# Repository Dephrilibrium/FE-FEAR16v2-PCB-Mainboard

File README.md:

# FEAR-Mainboard
This repository contains the KiCAD-design files of the F(ield) E(mission) A(rray) R(egulation) current control circuit board.

Note: This project is part of the SubModule-repository [FE-FEAR16v2][FE-FEAR16v2-SubmoduleRepo], where you can find sub-repositories for shield-PCBs and the firmware.

# Description
The board has two areas. A low-voltage side (5V USB for computer connection, top left) which is galvanically isolated up to 1500V from the high voltage side (rest of the PCB).

The board uses a USB-C jack on the low-voltage side of the board for communication. The USB-C can also be used as AC power supply, but for this, a USB-Hub with an AC-power adapter is recommended (depending on the amount of shields and their power-use). Alternatively, a 12V screw-terminal is added as option for an external 12V AC power supply. The option if 5V USB or 12V external supply is selected by a solder-jumper. (Note: +5V or +12V needs different DCDC converter types for the +-15V supply voltage on the high-voltage side!)

The board communicates via USB by providing a virtual COM-Port on the computer. The serial connection from the FT232 for board-internal communication is transferred from the low-voltage side to the high-voltage side via optocouplers and there connected to a TIVA-Launchpad, providing the microcontroller (µC). The Launchpad runs a terminal where you can query different commands e.g. querying measurement values, etc. The µC uses SPI connections for the ADCs and DACs.

ADCs and DACs have different supplies for logic (digital signals) and references (analog) and provide 2 ADC-inputs (VShnt0..15 and VDrp0..15) for measurements and 1x DAC-output (DAC0..15) for controls to each of the shields. Each ADC and DAC has only 8 inputs. Therefore, 2 of them each can be daisy-chained together to achieve 16 in-/outputs for VShnt, VDrp and DAC.

The ADC and DAC range is by default &pm;10V. However, the ranges can be adjusted within the firmware in the ADC/DAC-wrapper sourcecodes.

# Firmware
The board-firmware can be found in the [FE-FEAR16v2 Submodule-Repo][FE-FEAR16v2-SubmoduleRepo] and needs to be flashed onto the µC of the LaunchPad. Instructions and command-documentation can be found in the firmware-repository.

# Daisy-Chains
ADCs and DACs only have 8 In-/Outputs per chip. For enough In-/Outputs for up to 16 shields, 2 ADCs or DACs can be daisy-chained together. 1 and 2 chips per ADC- and DAC-chain were tested. When using only 1 chip per ADC-/DAC-chain, the MISO (SPI data in) and MOSI (SPI data out) pins of the empty ADC-footprint needs to be shorted. The connection is indicated by the silk-screen:

The firmware handles this via software defines (described in the firmware-repository).

[FE-FEAR16v2-SubmoduleRepo]: https://github.com/Dephrilibrium/FE-FEAR16v2

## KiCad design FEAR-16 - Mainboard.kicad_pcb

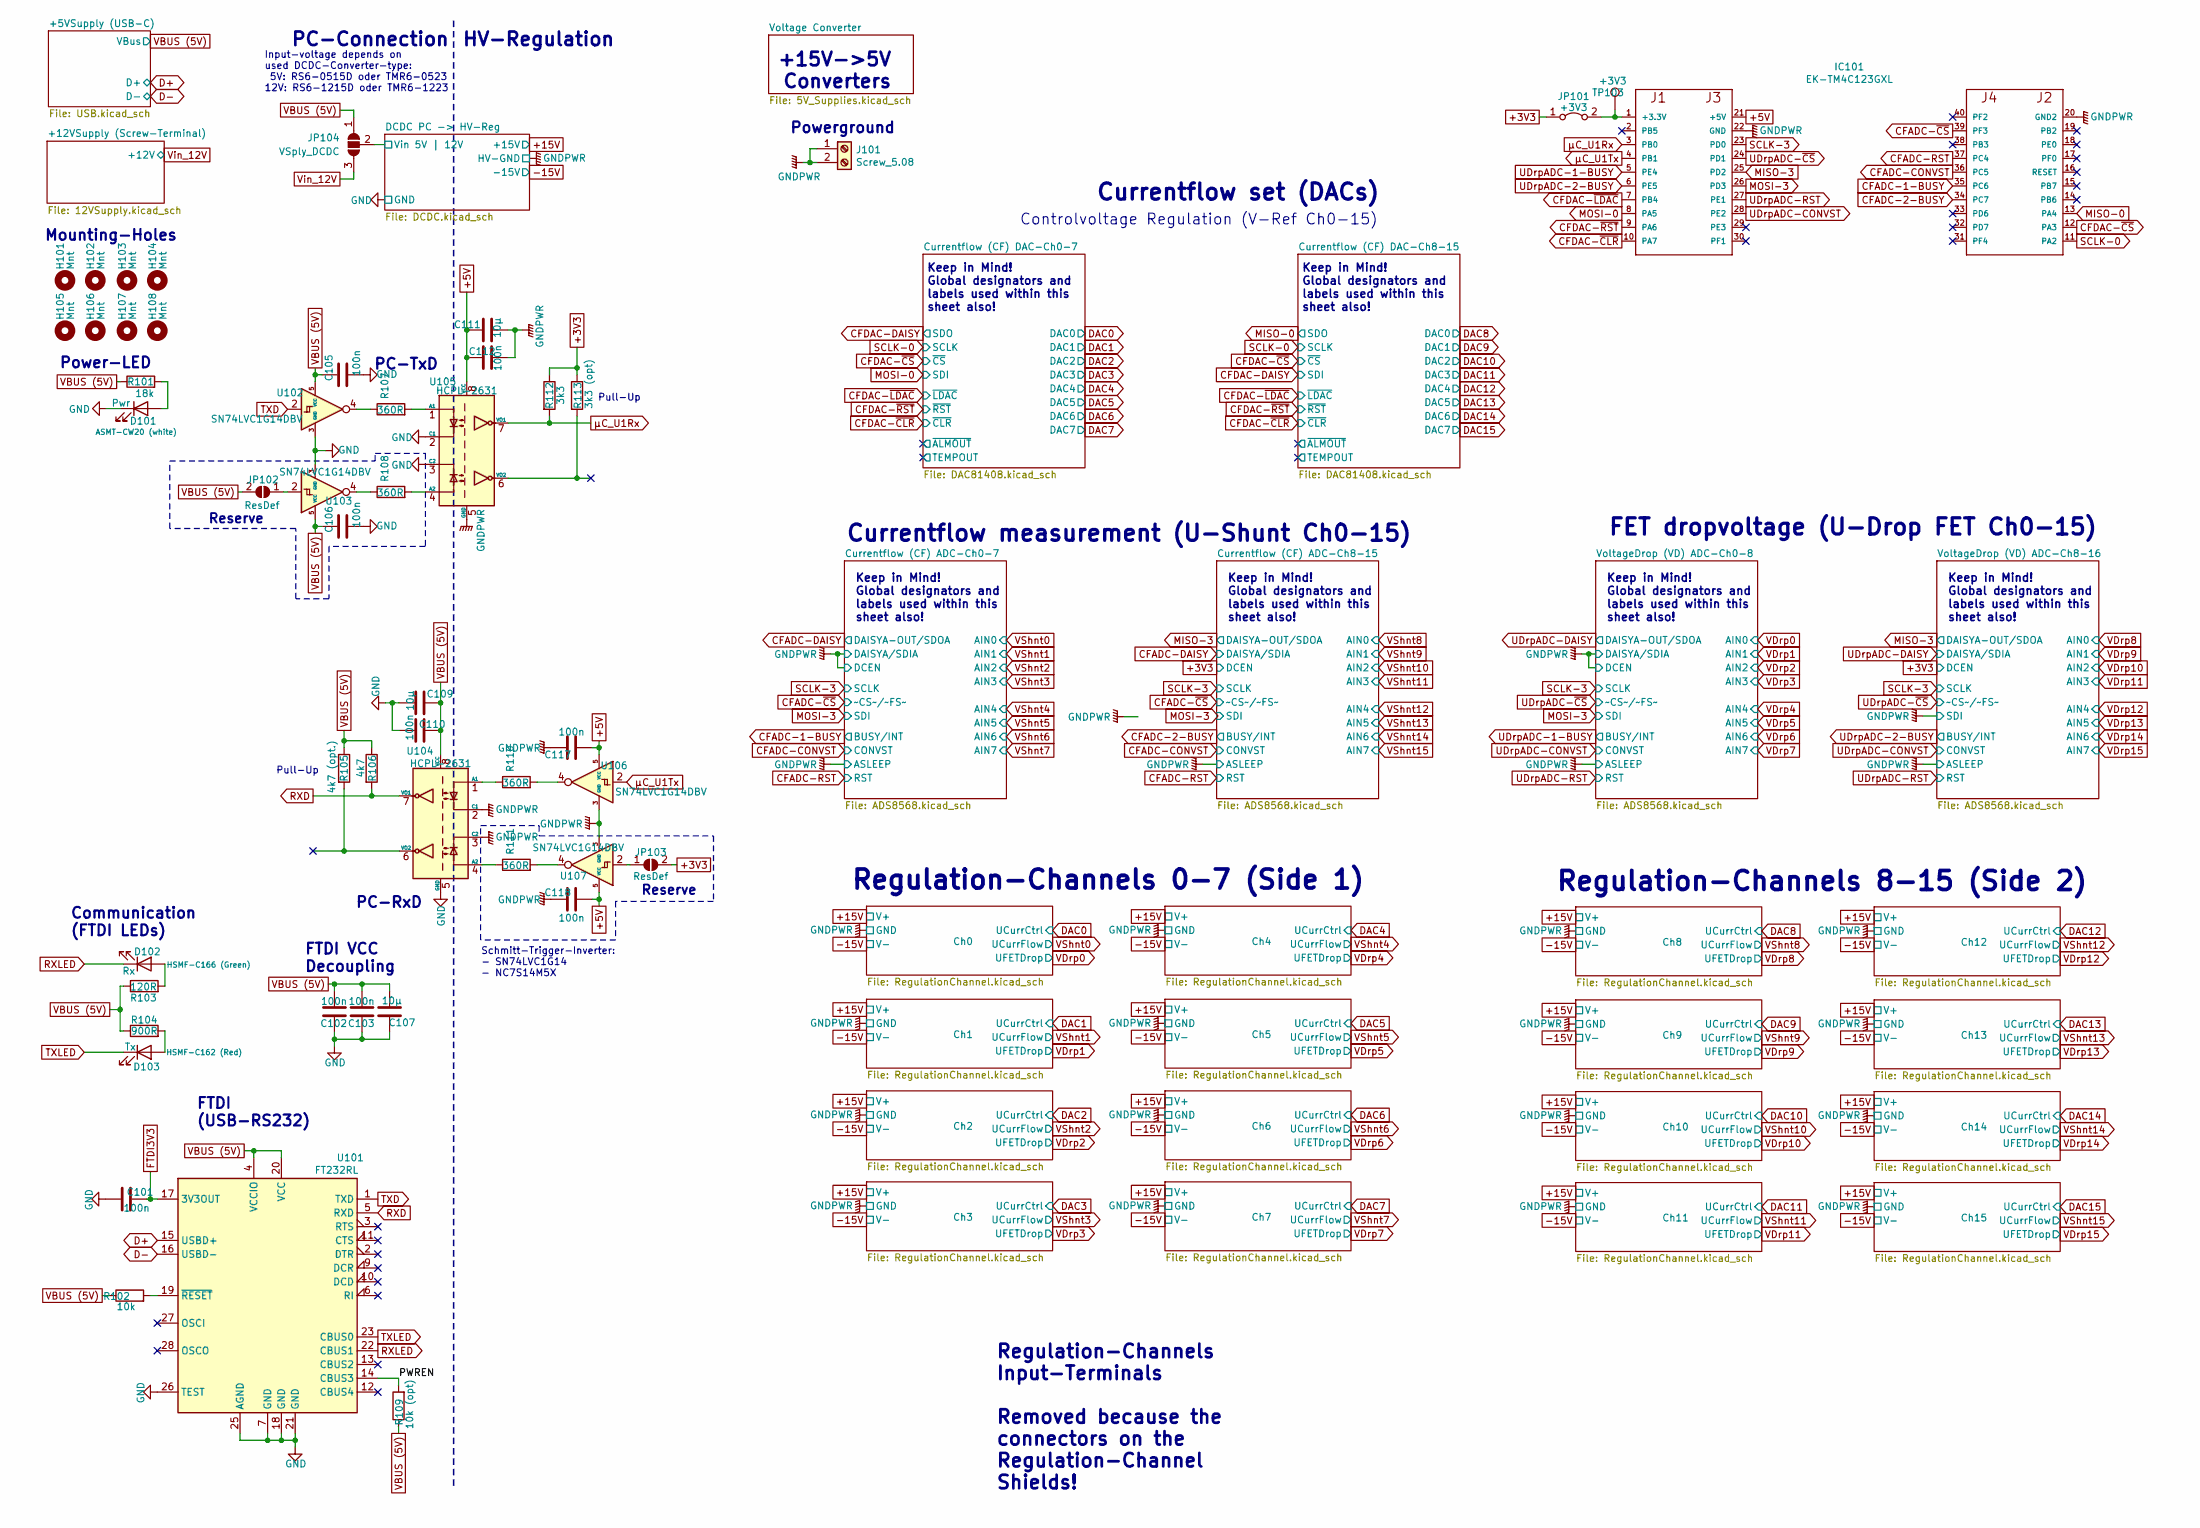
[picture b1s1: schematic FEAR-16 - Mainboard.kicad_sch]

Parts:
C101, C102, C103, C105, C106, C110, C112, C117, C118: 100n; C_0603_1608Metric
C107, C109, C111: 10µ; C_0805_2012Metric
D101: Pwr; LED_0603_1608Metric
D102: Rx; LED_0603_1608Metric
D103: Tx; LED_0603_1608Metric
H101, H102, H103, H104, H105, H106, H107, H108: Mnt; MountingHole_3.2mm_M3
IC101: EK-TM4C123GXL; TM4C123LAUNCHPAD
J101: Screw_5.08; TerminalBlock_RND_205-00232_1x02_P5.08mm_Horizontal
JP101: +3V3; PinHeader_1x02_P2.54mm_Vertical
JP102, JP103: ResDef; SolderJumper-2_P1.3mm_Open_RoundedPad1.0x1.5mm
JP104: VSply_DCDC; SolderJumper-3_P1.3mm_Open_RoundedPad1.0x1.5mm
R101: 18k; R_0603_1608Metric
R102: 10k; R_0603_1608Metric
R103: 120R; R_0603_1608Metric
R104: 900R; R_0603_1608Metric
R105: 4k7 (opt.); R_0603_1608Metric
R106: 4k7; R_0603_1608Metric
R107, R108, R110, R111: 360R; R_0603_1608Metric
R109: 10k (opt); R_0603_1608Metric
R112: 3k3; R_0603_1608Metric
R113: 3k3 (opt); R_0603_1608Metric
TP103: +3V3; TestPoint_Pad_D1.5mm
U101: FT232RL; SSOP-28_5.3x10.2mm_P0.65mm
U102, U103, U106, U107: SN74LVC1G14DBV; SOT-23-5
U104, U105: HCPL-2631; DIP-8_W7.62mm

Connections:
+3V3: JP101.1 (A), JP103.2 (B), R112.1, R113.1; also elsewhere on the board
+5V: C111.1, C112.2, C117.1, C118.1, IC101.21 (+5V), U105.8 (VCC), U106.5 (VCC), U107.5 (VCC); also elsewhere on the board
/DCDC PC -> HV-Reg/Vin 5V | 12V: JP104.2 (C); also elsewhere on the board
/PWREN: R109.2, U101.14 (CBUS3)
CFADC-1-BUSY: IC101.35 (PC6); also elsewhere on the board
CFADC-2-BUSY: IC101.34 (PC7); also elsewhere on the board
CFADC-CONVST: IC101.36 (PC5); also elsewhere on the board
CFADC-RST: IC101.37 (PC4); also elsewhere on the board
CFADC-~CS: IC101.39 (PF3); also elsewhere on the board
CFDAC-~CLR: IC101.10 (PA7); also elsewhere on the board
CFDAC-~CS: IC101.12 (PA3); also elsewhere on the board
CFDAC-~LDAC: IC101.7 (PB4); also elsewhere on the board
CFDAC-~RST: IC101.9 (PA6); also elsewhere on the board
D+: U101.15 (USBD+); also elsewhere on the board
D-: U101.16 (USBD-); also elsewhere on the board
FTDI3V3: C101.2, U101.17 (3V3OUT)
GND: C101.1, C102.1, C103.1, C105.2, C106.2, C107.2, C109.2, C110.1, D101.1 (K), U101.7 (GND), U101.18 (GND), U101.21 (GND), U101.25 (AGND), U101.26 (TEST), U102.3 (GND), U103.3 (GND), U104.5 (GND), U105.2 (C1), U105.3 (C2); also elsewhere on the board
GNDPWR: C111.2, C112.1, C117.2, C118.2, IC101.20 (GND2), IC101.22 (GND), J101.1, J101.2, U104.2 (C1), U104.3 (C2), U105.5 (GND), U106.3 (GND), U107.3 (GND); also elsewhere on the board
MISO-0: IC101.13 (PA4); also elsewhere on the board
MISO-3: IC101.25 (PD2); also elsewhere on the board
MOSI-0: IC101.8 (PA5); also elsewhere on the board
MOSI-3: IC101.26 (PD3); also elsewhere on the board
unnamed: D101.2 (A), R101.2
unnamed: D102.2 (A), R103.2
unnamed: D103.2 (A), R104.2
unnamed: IC101.1 (+3.3V), JP101.2 (B), TP103.1
unnamed: JP102.1 (A), U103.2
unnamed: JP103.1 (A), U107.2
unnamed: R107.1, U102.4
unnamed: R108.1, U103.4
unnamed: R110.2, U106.4
unnamed: R111.2, U107.4
unnamed: R102.2, U101.19 (~RESET)
unnamed: R110.1, U104.1 (A1)
unnamed: R111.1, U104.4 (A2)
unnamed: R107.2, U105.1 (A1)
unnamed: R108.2, U105.4 (A2)
RXD: R106.2, U101.5 (RXD), U104.7 (VO1)
RXLED: D102.1 (K), U101.22 (CBUS1)
SCLK-0: IC101.11 (PA2); also elsewhere on the board
SCLK-3: IC101.23 (PD0); also elsewhere on the board
TXD: U101.1 (TXD), U102.2
TXLED: D103.1 (K), U101.23 (CBUS0)
UDrpADC-1-BUSY: IC101.5 (PE4); also elsewhere on the board
UDrpADC-2-BUSY: IC101.6 (PE5); also elsewhere on the board
UDrpADC-CONVST: IC101.28 (PE2); also elsewhere on the board
UDrpADC-RST: IC101.27 (PE1); also elsewhere on the board
UDrpADC-~CS: IC101.24 (PD1); also elsewhere on the board
VBUS (5V): C102.2, C103.2, C105.1, C106.1, C107.1, C109.1, C110.2, JP102.2 (B), JP104.1 (A), R101.1, R102.1, R103.1, R104.1, R105.1, R106.1, R109.1, U101.4 (VCCIO), U101.20 (VCC), U102.5 (VCC), U103.5 (VCC), U104.8 (VCC); also elsewhere on the board
Vin_12V: JP104.3 (B); also elsewhere on the board
µC_U1Rx: IC101.3 (PB0), R112.2, U105.7 (VO1)
µC_U1Tx: IC101.4 (PB1), U106.2

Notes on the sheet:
Power-LED
Controlvoltage Regulation (V-Ref Ch0-15)
Keep in Mind! Global designators and labels used within this sheet also!
Reserve
Regulation-Channels 8-15 (Side 2)
Regulation-Channels Input-Terminals Removed because the connectors on the Regulation-Channel Shields!
Mounting-Holes
FTDI (USB-RS232)
HV-Regulation
PC-RxD
Input-voltage depends on used DCDC-Converter-type: 5V: RS6-0515D oder TMR6-0523 12V: RS6-1215D oder TMR6-1223
Communication (FTDI LEDs)
Regulation-Channels 0-7 (Side 1)
Pull-Up
Powerground
Currentflow measurement (U-Shunt Ch0-15)
FET dropvoltage (U-Drop FET Ch0-15)
PC-TxD
Currentflow set (DACs)
PC-Connection
+15V->5V Converters
Schmitt-Trigger-Inverter: - SN74LVC1G14 - NC7S14M5X
FTDI VCC Decoupling

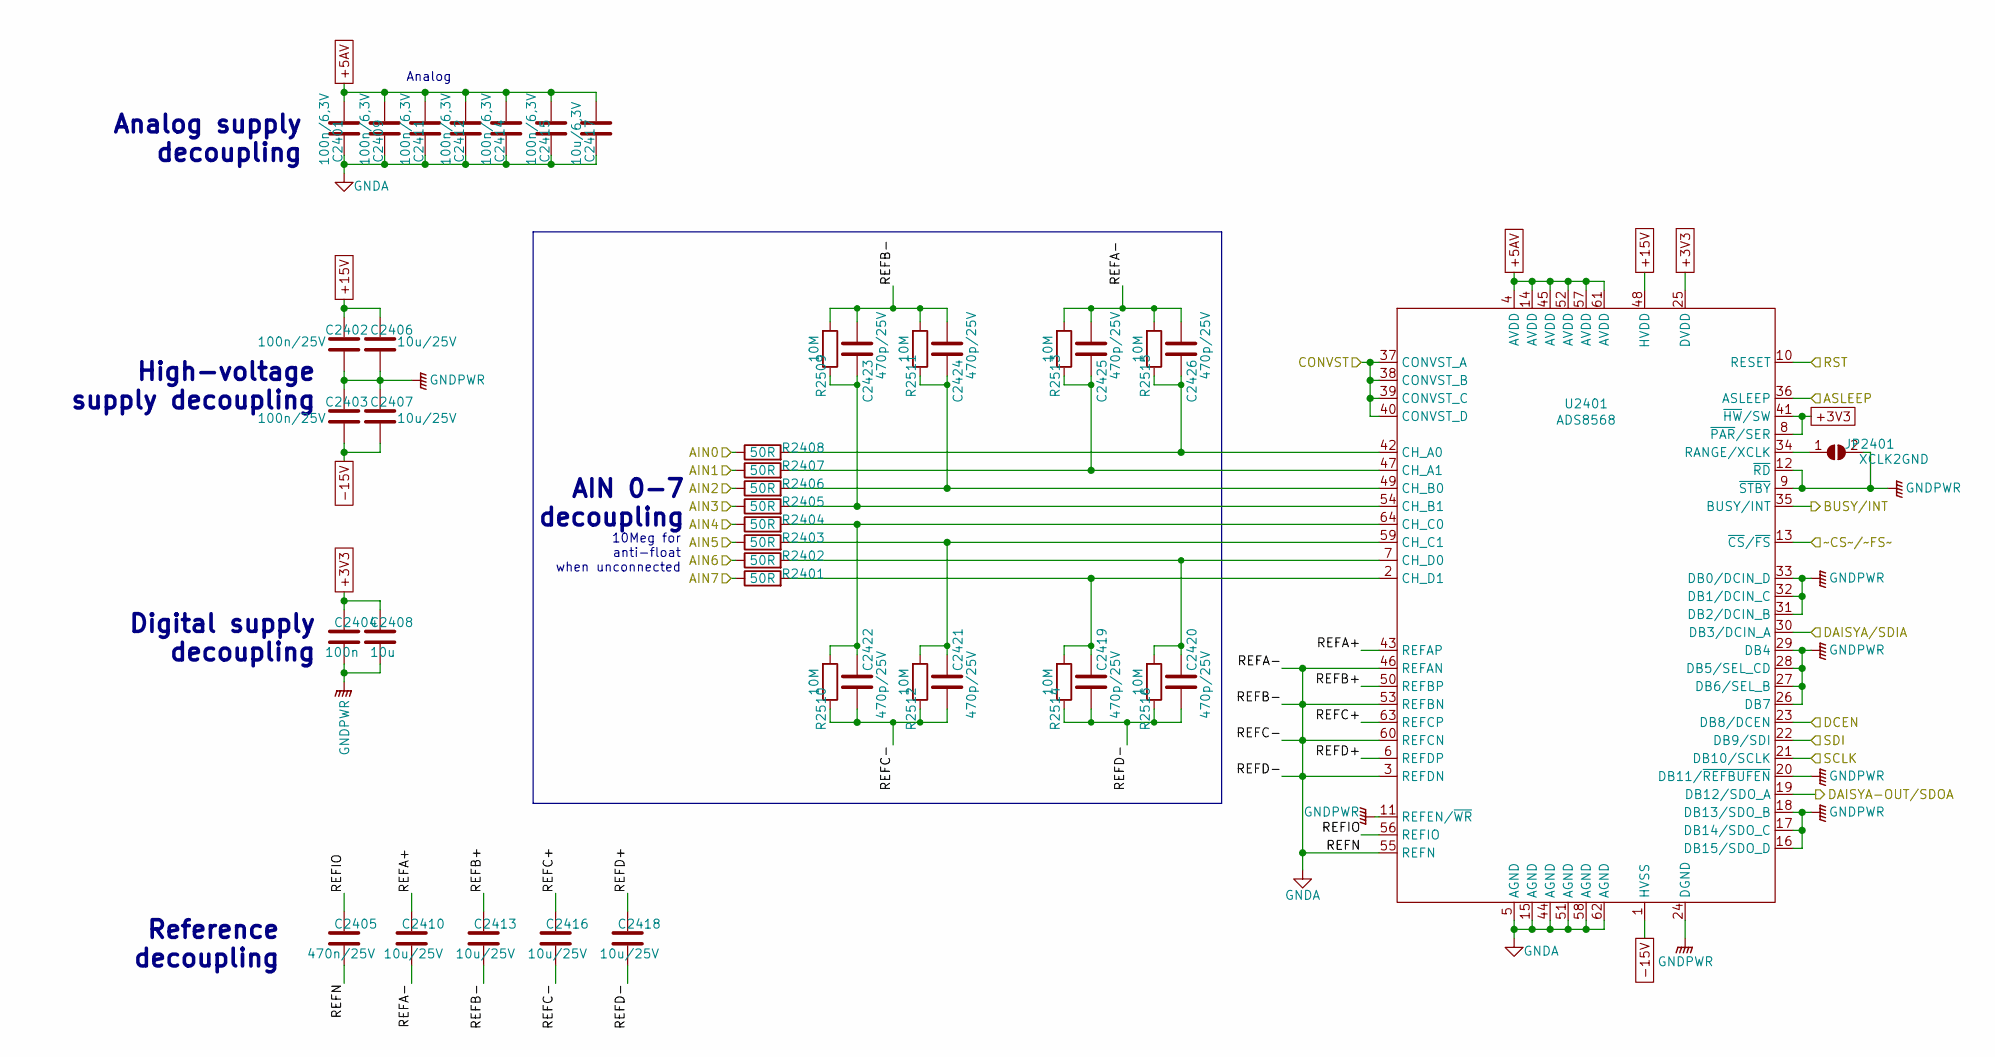
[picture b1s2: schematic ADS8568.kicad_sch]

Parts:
C2401, C2409, C2411, C2412, C2414, C2415: 100n/6,3V; C_0603_1608Metric
C2402, C2403: 100n/25V; C_0603_1608Metric
C2404: 100n; C_0603_1608Metric
C2405: 470n/25V; C_0603_1608Metric
C2406, C2407, C2410, C2413, C2416, C2418: 10u/25V; C_0805_2012Metric
C2408: 10u; C_0805_2012Metric
C2417: 10u/6,3V; C_0805_2012Metric
C2419, C2420, C2421, C2422, C2423, C2424, C2425, C2426: 470p/25V; C_0603_1608Metric
JP2401: XCLK2GND; Jumper_0.5x0.5
R2401, R2402, R2403, R2404, R2405, R2406, R2407, R2408: 50R; R_0603_1608Metric
R2509, R2510, R2511, R2512, R2513, R2514, R2515, R2516: 10M; R_0603_1608Metric
U2401: ADS8568; LQFP-64_10x10mm_P0.5mm

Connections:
+3V3: C2404.1, C2408.1, U2401.8 (~PAR/SER), U2401.25 (DVDD), U2401.41 (~HW/SW); also elsewhere on the board
+5AV: C2401.1, C2409.1, C2411.1, C2412.1, C2414.1, C2415.1, C2417.1, U2401.4 (AVDD), U2401.14 (AVDD), U2401.45 (AVDD), U2401.52 (AVDD), U2401.57 (AVDD), U2401.61 (AVDD); also elsewhere on the board
+15V: C2402.1, C2406.1, U2401.48 (HVDD); also elsewhere on the board
-15V: C2403.2, C2407.2, U2401.1 (HVSS); also elsewhere on the board
/VoltageDrop (VD) ADC-Ch0-8/REFA+: C2410.1, U2401.43 (REFAP)
/VoltageDrop (VD) ADC-Ch0-8/REFB+: C2413.1, U2401.50 (REFBP)
/VoltageDrop (VD) ADC-Ch0-8/REFC+: C2416.1, U2401.63 (REFCP)
/VoltageDrop (VD) ADC-Ch0-8/REFD+: C2418.1, U2401.6 (REFDP)
/VoltageDrop (VD) ADC-Ch0-8/REFIO: C2405.1, U2401.56 (REFIO)
GNDA: C2401.2, C2405.2, C2409.2, C2410.2, C2411.2, C2412.2, C2413.2, C2414.2, C2415.2, C2416.2, C2417.2, C2418.2, C2419.2, C2420.2, C2421.2, C2422.2, C2423.2, C2424.2, C2425.2, C2426.2, R2509.2, R2510.1, R2511.2, R2512.1, R2513.2, R2514.1, R2515.2, R2516.1, U2401.3 (REFDN), U2401.5 (AGND), U2401.15 (AGND), U2401.44 (AGND), U2401.46 (REFAN), U2401.51 (AGND), U2401.53 (REFBN), U2401.55 (REFN), U2401.58 (AGND), U2401.60 (REFCN), U2401.62 (AGND); also elsewhere on the board
GNDPWR: C2402.2, C2403.1, C2404.2, C2406.2, C2407.1, C2408.2, JP2401.2 (B), U2401.9 (~STBY), U2401.11 (REFEN/~WR), U2401.12 (~RD), U2401.16 (DB15/SDO_D), U2401.17 (DB14/SDO_C), U2401.18 (DB13/SDO_B), U2401.20 (DB11/~REFBUFEN), U2401.23 (DB8/DCEN), U2401.24 (DGND), U2401.26 (DB7), U2401.27 (DB6/SEL_B), U2401.28 (DB5/SEL_CD), U2401.29 (DB4), U2401.30 (DB3/DCIN_A), U2401.31 (DB2/DCIN_B), U2401.32 (DB1/DCIN_C), U2401.33 (DB0/DCIN_D), U2401.36 (ASLEEP); also elsewhere on the board
MOSI-3: U2401.22 (DB9/SDI); also elsewhere on the board
unnamed: JP2401.1 (A), U2401.34 (RANGE/XCLK)
unnamed: C2426.1, R2408.2, R2515.1, U2401.42 (CH_A0)
unnamed: C2425.1, R2407.2, R2513.1, U2401.47 (CH_A1)
unnamed: C2424.1, R2406.2, R2511.1, U2401.49 (CH_B0)
unnamed: C2423.1, R2405.2, R2509.1, U2401.54 (CH_B1)
unnamed: C2422.1, R2404.2, R2510.2, U2401.64 (CH_C0)
unnamed: C2421.1, R2403.2, R2512.2, U2401.59 (CH_C1)
unnamed: C2420.1, R2402.2, R2516.2, U2401.7 (CH_D0)
unnamed: C2419.1, R2401.2, R2514.2, U2401.2 (CH_D1)
SCLK-3: U2401.21 (DB10/SCLK); also elsewhere on the board
UDrpADC-1-BUSY: U2401.35 (BUSY/INT); also elsewhere on the board
UDrpADC-CONVST: U2401.37 (CONVST_A), U2401.38 (CONVST_B), U2401.39 (CONVST_C), U2401.40 (CONVST_D); also elsewhere on the board
UDrpADC-DAISY: U2401.19 (DB12/SDO_A); also elsewhere on the board
UDrpADC-RST: U2401.10 (RESET); also elsewhere on the board
UDrpADC-~CS: U2401.13 (~CS/~FS); also elsewhere on the board
VDrp0: R2408.1; also elsewhere on the board
VDrp1: R2407.1; also elsewhere on the board
VDrp2: R2406.1; also elsewhere on the board
VDrp3: R2405.1; also elsewhere on the board
VDrp4: R2404.1; also elsewhere on the board
VDrp5: R2403.1; also elsewhere on the board
VDrp6: R2402.1; also elsewhere on the board
VDrp7: R2401.1; also elsewhere on the board

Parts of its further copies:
C1301, C1309, C1311, C1312, C1314, C1315, C2201, C2209, C2211, C2212, C2214, C2215, C2501, C2509, C2511, C2512, C2514, C2515: 100n/6,3V; C_0603_1608Metric
C1302, C1303, C2202, C2203, C2502, C2503: 100n/25V; C_0603_1608Metric
C1304, C2204, C2504: 100n; C_0603_1608Metric
C1305, C2205, C2505: 470n/25V; C_0603_1608Metric
C1306, C1307, C1310, C1313, C1316, C1318, C2206, C2207, C2210, C2213, C2216, C2218, C2506, C2507, C2510, C2513, C2516, C2518: 10u/25V; C_0805_2012Metric
C1308, C2208, C2508: 10u; C_0805_2012Metric
C1317, C2217, C2517: 10u/6,3V; C_0805_2012Metric
C1319, C1320, C1321, C1322, C1323, C1324, C1325, C1326, C2219, C2220, C2221, C2222, C2223, C2224, C2225, C2226, C2519, C2520, C2521, C2522, C2523, C2524, C2525, C2526: 470p/25V; C_0603_1608Metric
JP1301, JP2201, JP2501: XCLK2GND; Jumper_0.5x0.5
R1301, R1302, R1303, R1304, R1305, R1306, R1307, R1308, R2201, R2202, R2203, R2204, R2205, R2206, R2207, R2208, R2501, R2502, R2503, R2504, R2505, R2506, R2507, R2508: 50R; R_0603_1608Metric
R1309, R1310, R1311, R1312, R1313, R1314, R1315, R1316, R2302, R2303, R2304, R2305, R2306, R2307, R2308, R2309, R2601, R2602, R2603, R2604, R2605, R2606, R2607, R2608: 10M; R_0603_1608Metric
U1301, U2201, U2501: ADS8568; LQFP-64_10x10mm_P0.5mm

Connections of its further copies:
+3V3: C1304.1, C1308.1, C2204.1, C2208.1, C2504.1, C2508.1, U1301.8 (~PAR/SER), U1301.25 (DVDD), U1301.41 (~HW/SW), U2201.8 (~PAR/SER), U2201.23 (DB8/DCEN), U2201.25 (DVDD), U2201.41 (~HW/SW), U2501.8 (~PAR/SER), U2501.23 (DB8/DCEN), U2501.25 (DVDD), U2501.41 (~HW/SW); also elsewhere on the board
+5AV: C1301.1, C1309.1, C1311.1, C1312.1, C1314.1, C1315.1, C1317.1, C2201.1, C2209.1, C2211.1, C2212.1, C2214.1, C2215.1, C2217.1, C2501.1, C2509.1, C2511.1, C2512.1, C2514.1, C2515.1, C2517.1, U1301.4 (AVDD), U1301.14 (AVDD), U1301.45 (AVDD), U1301.52 (AVDD), U1301.57 (AVDD), U1301.61 (AVDD), U2201.4 (AVDD), U2201.14 (AVDD), U2201.45 (AVDD), U2201.52 (AVDD), U2201.57 (AVDD), U2201.61 (AVDD), U2501.4 (AVDD), U2501.14 (AVDD), U2501.45 (AVDD), U2501.52 (AVDD), U2501.57 (AVDD), U2501.61 (AVDD); also elsewhere on the board
+15V: C1302.1, C1306.1, C2202.1, C2206.1, C2502.1, C2506.1, U1301.48 (HVDD), U2201.48 (HVDD), U2501.48 (HVDD); also elsewhere on the board
-15V: C1303.2, C1307.2, C2203.2, C2207.2, C2503.2, C2507.2, U1301.1 (HVSS), U2201.1 (HVSS), U2501.1 (HVSS); also elsewhere on the board
/Currentflow (CF) ADC-Ch0-7/REFA+: C1310.1, U1301.43 (REFAP)
/Currentflow (CF) ADC-Ch0-7/REFB+: C1313.1, U1301.50 (REFBP)
/Currentflow (CF) ADC-Ch0-7/REFC+: C1316.1, U1301.63 (REFCP)
/Currentflow (CF) ADC-Ch0-7/REFD+: C1318.1, U1301.6 (REFDP)
/Currentflow (CF) ADC-Ch0-7/REFIO: C1305.1, U1301.56 (REFIO)
/Currentflow (CF) ADC-Ch8-15/REFA+: C2210.1, U2201.43 (REFAP)
/Currentflow (CF) ADC-Ch8-15/REFB+: C2213.1, U2201.50 (REFBP)
/Currentflow (CF) ADC-Ch8-15/REFC+: C2216.1, U2201.63 (REFCP)
/Currentflow (CF) ADC-Ch8-15/REFD+: C2218.1, U2201.6 (REFDP)
/Currentflow (CF) ADC-Ch8-15/REFIO: C2205.1, U2201.56 (REFIO)
/Currentflow (CF) ADC-Ch8-15/SDI: U2201.22 (DB9/SDI)
/VoltageDrop (VD) ADC-Ch8-16/REFA+: C2510.1, U2501.43 (REFAP)
/VoltageDrop (VD) ADC-Ch8-16/REFB+: C2513.1, U2501.50 (REFBP)
/VoltageDrop (VD) ADC-Ch8-16/REFC+: C2516.1, U2501.63 (REFCP)
/VoltageDrop (VD) ADC-Ch8-16/REFD+: C2518.1, U2501.6 (REFDP)
/VoltageDrop (VD) ADC-Ch8-16/REFIO: C2505.1, U2501.56 (REFIO)
CFADC-1-BUSY: U1301.35 (BUSY/INT); also elsewhere on the board
CFADC-2-BUSY: U2201.35 (BUSY/INT); also elsewhere on the board
CFADC-CONVST: U1301.37 (CONVST_A), U1301.38 (CONVST_B), U1301.39 (CONVST_C), U1301.40 (CONVST_D), U2201.37 (CONVST_A), U2201.38 (CONVST_B), U2201.39 (CONVST_C), U2201.40 (CONVST_D); also elsewhere on the board
CFADC-DAISY: U1301.19 (DB12/SDO_A), U2201.30 (DB3/DCIN_A)
CFADC-RST: U1301.10 (RESET), U2201.10 (RESET); also elsewhere on the board
CFADC-~CS: U1301.13 (~CS/~FS), U2201.13 (~CS/~FS); also elsewhere on the board
GNDA: C1301.2, C1305.2, C1309.2, C1310.2, C1311.2, C1312.2, C1313.2, C1314.2, C1315.2, C1316.2, C1317.2, C1318.2, C1319.2, C1320.2, C1321.2, C1322.2, C1323.2, C1324.2, C1325.2, C1326.2, C2201.2, C2205.2, C2209.2, C2210.2, C2211.2, C2212.2, C2213.2, C2214.2, C2215.2, C2216.2, C2217.2, C2218.2, C2219.2, C2220.2, C2221.2, C2222.2, C2223.2, C2224.2, C2225.2, C2226.2, C2501.2, C2505.2, C2509.2, C2510.2, C2511.2, C2512.2, C2513.2, C2514.2, C2515.2, C2516.2, C2517.2, C2518.2, C2519.2, C2520.2, C2521.2, C2522.2, C2523.2, C2524.2, C2525.2, C2526.2, R1309.2, R1310.1, R1311.2, R1312.1, R1313.2, R1314.1, R1315.2, R1316.1, R2302.2, R2303.1, R2304.2, R2305.1, R2306.2, R2307.1, R2308.2, R2309.1, R2601.2, R2602.1, R2603.2, R2604.1, R2605.2, R2606.1, R2607.2, R2608.1, U1301.3 (REFDN), U1301.5 (AGND), U1301.15 (AGND), U1301.44 (AGND), U1301.46 (REFAN), U1301.51 (AGND), U1301.53 (REFBN), U1301.55 (REFN), U1301.58 (AGND), U1301.60 (REFCN), U1301.62 (AGND), U2201.3 (REFDN), U2201.5 (AGND), U2201.15 (AGND), U2201.44 (AGND), U2201.46 (REFAN), U2201.51 (AGND), U2201.53 (REFBN), U2201.55 (REFN), U2201.58 (AGND), U2201.60 (REFCN), U2201.62 (AGND), U2501.3 (REFDN), U2501.5 (AGND), U2501.15 (AGND), U2501.44 (AGND), U2501.46 (REFAN), U2501.51 (AGND), U2501.53 (REFBN), U2501.55 (REFN), U2501.58 (AGND), U2501.60 (REFCN), U2501.62 (AGND); also elsewhere on the board
GNDPWR: C1302.2, C1303.1, C1304.2, C1306.2, C1307.1, C1308.2, C2202.2, C2203.1, C2204.2, C2206.2, C2207.1, C2208.2, C2502.2, C2503.1, C2504.2, C2506.2, C2507.1, C2508.2, JP1301.2 (B), JP2201.2 (B), JP2501.2 (B), U1301.9 (~STBY), U1301.11 (REFEN/~WR), U1301.12 (~RD), U1301.16 (DB15/SDO_D), U1301.17 (DB14/SDO_C), U1301.18 (DB13/SDO_B), U1301.20 (DB11/~REFBUFEN), U1301.23 (DB8/DCEN), U1301.24 (DGND), U1301.26 (DB7), U1301.27 (DB6/SEL_B), U1301.28 (DB5/SEL_CD), U1301.29 (DB4), U1301.30 (DB3/DCIN_A), U1301.31 (DB2/DCIN_B), U1301.32 (DB1/DCIN_C), U1301.33 (DB0/DCIN_D), U1301.36 (ASLEEP), U2201.9 (~STBY), U2201.11 (REFEN/~WR), U2201.12 (~RD), U2201.16 (DB15/SDO_D), U2201.17 (DB14/SDO_C), U2201.18 (DB13/SDO_B), U2201.20 (DB11/~REFBUFEN), U2201.24 (DGND), U2201.26 (DB7), U2201.27 (DB6/SEL_B), U2201.28 (DB5/SEL_CD), U2201.29 (DB4), U2201.31 (DB2/DCIN_B), U2201.32 (DB1/DCIN_C), U2201.33 (DB0/DCIN_D), U2201.36 (ASLEEP), U2501.9 (~STBY), U2501.11 (REFEN/~WR), U2501.12 (~RD), U2501.16 (DB15/SDO_D), U2501.17 (DB14/SDO_C), U2501.18 (DB13/SDO_B), U2501.20 (DB11/~REFBUFEN), U2501.22 (DB9/SDI), U2501.24 (DGND), U2501.26 (DB7), U2501.27 (DB6/SEL_B), U2501.28 (DB5/SEL_CD), U2501.29 (DB4), U2501.31 (DB2/DCIN_B), U2501.32 (DB1/DCIN_C), U2501.33 (DB0/DCIN_D), U2501.36 (ASLEEP); also elsewhere on the board
MISO-3: U2201.19 (DB12/SDO_A), U2501.19 (DB12/SDO_A); also elsewhere on the board
MOSI-3: U1301.22 (DB9/SDI); also elsewhere on the board
unnamed: JP1301.1 (A), U1301.34 (RANGE/XCLK)
unnamed: JP2201.1 (A), U2201.34 (RANGE/XCLK)
unnamed: JP2501.1 (A), U2501.34 (RANGE/XCLK)
unnamed: C1326.1, R1308.2, R1315.1, U1301.42 (CH_A0)
unnamed: C1325.1, R1307.2, R1313.1, U1301.47 (CH_A1)
unnamed: C1324.1, R1306.2, R1311.1, U1301.49 (CH_B0)
unnamed: C1323.1, R1305.2, R1309.1, U1301.54 (CH_B1)
unnamed: C1322.1, R1304.2, R1310.2, U1301.64 (CH_C0)
unnamed: C1321.1, R1303.2, R1312.2, U1301.59 (CH_C1)
unnamed: C1320.1, R1302.2, R1316.2, U1301.7 (CH_D0)
unnamed: C1319.1, R1301.2, R1314.2, U1301.2 (CH_D1)
unnamed: C2226.1, R2208.2, R2308.1, U2201.42 (CH_A0)
unnamed: C2225.1, R2207.2, R2306.1, U2201.47 (CH_A1)
unnamed: C2224.1, R2206.2, R2304.1, U2201.49 (CH_B0)
unnamed: C2223.1, R2205.2, R2302.1, U2201.54 (CH_B1)
unnamed: C2222.1, R2204.2, R2303.2, U2201.64 (CH_C0)
unnamed: C2221.1, R2203.2, R2305.2, U2201.59 (CH_C1)
unnamed: C2220.1, R2202.2, R2309.2, U2201.7 (CH_D0)
unnamed: C2219.1, R2201.2, R2307.2, U2201.2 (CH_D1)
unnamed: C2526.1, R2508.2, R2607.1, U2501.42 (CH_A0)
unnamed: C2525.1, R2507.2, R2605.1, U2501.47 (CH_A1)
unnamed: C2524.1, R2506.2, R2603.1, U2501.49 (CH_B0)
unnamed: C2523.1, R2505.2, R2601.1, U2501.54 (CH_B1)
unnamed: C2522.1, R2504.2, R2602.2, U2501.64 (CH_C0)
unnamed: C2521.1, R2503.2, R2604.2, U2501.59 (CH_C1)
unnamed: C2520.1, R2502.2, R2608.2, U2501.7 (CH_D0)
unnamed: C2519.1, R2501.2, R2606.2, U2501.2 (CH_D1)
SCLK-3: U1301.21 (DB10/SCLK), U2201.21 (DB10/SCLK), U2501.21 (DB10/SCLK); also elsewhere on the board
UDrpADC-2-BUSY: U2501.35 (BUSY/INT); also elsewhere on the board
UDrpADC-CONVST: U2501.37 (CONVST_A), U2501.38 (CONVST_B), U2501.39 (CONVST_C), U2501.40 (CONVST_D); also elsewhere on the board
UDrpADC-DAISY: U2501.30 (DB3/DCIN_A); also elsewhere on the board
UDrpADC-RST: U2501.10 (RESET); also elsewhere on the board
UDrpADC-~CS: U2501.13 (~CS/~FS); also elsewhere on the board
VDrp8: R2508.1; also elsewhere on the board
VDrp9: R2507.1; also elsewhere on the board
VDrp10: R2506.1; also elsewhere on the board
VDrp11: R2505.1; also elsewhere on the board
VDrp12: R2504.1; also elsewhere on the board
VDrp13: R2503.1; also elsewhere on the board
VDrp14: R2502.1; also elsewhere on the board
VDrp15: R2501.1; also elsewhere on the board
VShnt0: R1308.1; also elsewhere on the board
VShnt1: R1307.1; also elsewhere on the board
VShnt2: R1306.1; also elsewhere on the board
VShnt3: R1305.1; also elsewhere on the board
VShnt4: R1304.1; also elsewhere on the board
VShnt5: R1303.1; also elsewhere on the board
VShnt6: R1302.1; also elsewhere on the board
VShnt7: R1301.1; also elsewhere on the board
VShnt8: R2208.1; also elsewhere on the board
VShnt9: R2207.1; also elsewhere on the board
VShnt10: R2206.1; also elsewhere on the board
VShnt11: R2205.1; also elsewhere on the board
VShnt12: R2204.1; also elsewhere on the board
VShnt13: R2203.1; also elsewhere on the board
VShnt14: R2202.1; also elsewhere on the board
VShnt15: R2201.1; also elsewhere on the board

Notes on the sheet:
Analog
High-voltage supply decoupling
AIN 0-7 decoupling
10Meg for anti-float when unconnected
Reference decoupling
Digital supply decoupling
Analog supply decoupling

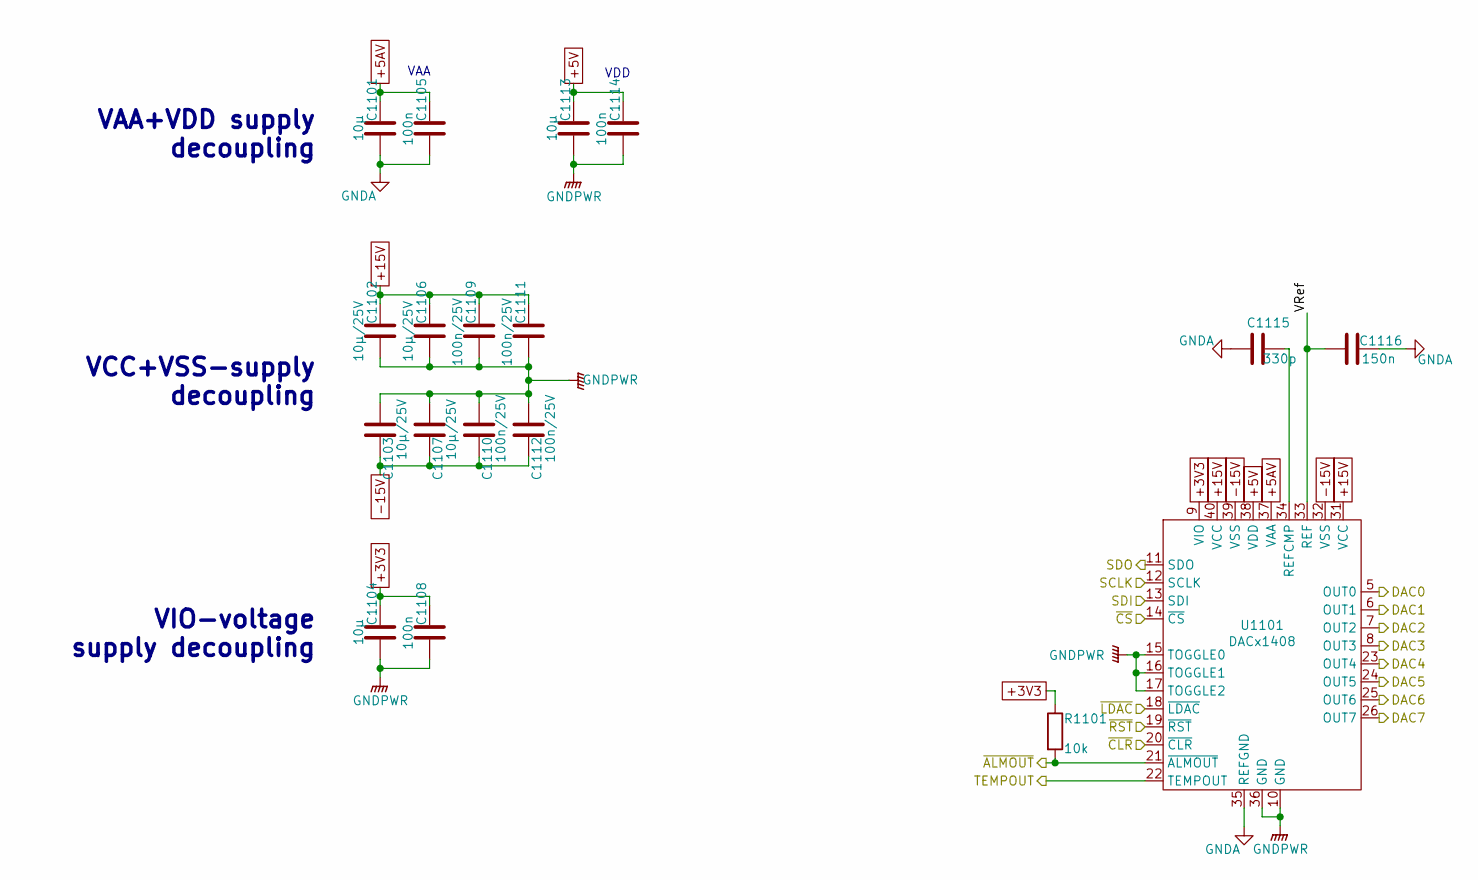
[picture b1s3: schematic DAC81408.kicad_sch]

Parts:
C1101, C1104, C1113: 10µ; C_0805_2012Metric
C1102, C1103, C1106, C1107: 10µ/25V; C_0805_2012Metric
C1105, C1108, C1114: 100n; C_0603_1608Metric
C1109, C1110, C1111, C1112: 100n/25V; C_0603_1608Metric
C1115: 330p; C_0603_1608Metric
C1116: 150n; C_0603_1608Metric
R1101: 10k; R_0603_1608Metric
U1101: DACx1408; HVQFN-40-1EP_6x6mm_P0.5mm_EP4.1x4.1mm_ThermalVias

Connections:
+3V3: C1104.1, C1108.1, R1101.1, U1101.9 (VIO); also elsewhere on the board
+5AV: C1101.1, C1105.1, U1101.37 (VAA); also elsewhere on the board
+5V: C1113.1, C1114.1, U1101.38 (VDD); also elsewhere on the board
+15V: C1102.1, C1106.1, C1109.1, C1111.1, U1101.31 (VCC), U1101.40 (VCC); also elsewhere on the board
-15V: C1103.1, C1107.1, C1110.1, C1112.1, U1101.32 (VSS), U1101.39 (VSS); also elsewhere on the board
/Currentflow (CF) DAC-Ch0-7/TEMPOUT: U1101.22 (TEMPOUT)
/Currentflow (CF) DAC-Ch0-7/VRef: C1116.2, U1101.33 (REF)
/Currentflow (CF) DAC-Ch0-7/~ALMOUT: R1101.2, U1101.21 (~ALMOUT)
CFDAC-DAISY: U1101.11 (SDO); also elsewhere on the board
CFDAC-~CLR: U1101.20 (~CLR); also elsewhere on the board
CFDAC-~CS: U1101.14 (~CS); also elsewhere on the board
CFDAC-~LDAC: U1101.18 (~LDAC); also elsewhere on the board
CFDAC-~RST: U1101.19 (~RST); also elsewhere on the board
DAC0: U1101.5 (OUT0); also elsewhere on the board
DAC1: U1101.6 (OUT1); also elsewhere on the board
DAC2: U1101.7 (OUT2); also elsewhere on the board
DAC3: U1101.8 (OUT3); also elsewhere on the board
DAC4: U1101.23 (OUT4); also elsewhere on the board
DAC5: U1101.24 (OUT5); also elsewhere on the board
DAC6: U1101.25 (OUT6); also elsewhere on the board
DAC7: U1101.26 (OUT7); also elsewhere on the board
GNDA: C1101.2, C1105.2, C1115.2, C1116.1, U1101.35 (REFGND); also elsewhere on the board
GNDPWR: C1102.2, C1103.2, C1104.2, C1106.2, C1107.2, C1108.2, C1109.2, C1110.2, C1111.2, C1112.2, C1113.2, C1114.2, U1101.10 (GND), U1101.15 (TOGGLE0), U1101.16 (TOGGLE1), U1101.17 (TOGGLE2), U1101.36 (GND); also elsewhere on the board
MOSI-0: U1101.13 (SDI); also elsewhere on the board
unnamed: C1115.1, U1101.34 (REFCMP)
SCLK-0: U1101.12 (SCLK); also elsewhere on the board

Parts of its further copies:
C2301, C2304, C2313: 10µ; C_0805_2012Metric
C2302, C2303, C2306, C2307: 10µ/25V; C_0805_2012Metric
C2305, C2308, C2314: 100n; C_0603_1608Metric
C2309, C2310, C2311, C2312: 100n/25V; C_0603_1608Metric
C2315: 330p; C_0603_1608Metric
C2316: 150n; C_0603_1608Metric
R2301: 10k; R_0603_1608Metric
U2301: DACx1408; HVQFN-40-1EP_6x6mm_P0.5mm_EP4.1x4.1mm_ThermalVias

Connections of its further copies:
+3V3: C2304.1, C2308.1, R2301.1, U2301.9 (VIO); also elsewhere on the board
+5AV: C2301.1, C2305.1, U2301.37 (VAA); also elsewhere on the board
+5V: C2313.1, C2314.1, U2301.38 (VDD); also elsewhere on the board
+15V: C2302.1, C2306.1, C2309.1, C2311.1, U2301.31 (VCC), U2301.40 (VCC); also elsewhere on the board
-15V: C2303.1, C2307.1, C2310.1, C2312.1, U2301.32 (VSS), U2301.39 (VSS); also elsewhere on the board
/Currentflow (CF) DAC-Ch8-15/TEMPOUT: U2301.22 (TEMPOUT)
/Currentflow (CF) DAC-Ch8-15/VRef: C2316.2, U2301.33 (REF)
/Currentflow (CF) DAC-Ch8-15/~ALMOUT: R2301.2, U2301.21 (~ALMOUT)
CFDAC-DAISY: U2301.13 (SDI); also elsewhere on the board
CFDAC-~CLR: U2301.20 (~CLR); also elsewhere on the board
CFDAC-~CS: U2301.14 (~CS); also elsewhere on the board
CFDAC-~LDAC: U2301.18 (~LDAC); also elsewhere on the board
CFDAC-~RST: U2301.19 (~RST); also elsewhere on the board
DAC8: U2301.5 (OUT0); also elsewhere on the board
DAC9: U2301.6 (OUT1); also elsewhere on the board
DAC10: U2301.7 (OUT2); also elsewhere on the board
DAC11: U2301.8 (OUT3); also elsewhere on the board
DAC12: U2301.23 (OUT4); also elsewhere on the board
DAC13: U2301.24 (OUT5); also elsewhere on the board
DAC14: U2301.25 (OUT6); also elsewhere on the board
DAC15: U2301.26 (OUT7); also elsewhere on the board
GNDA: C2301.2, C2305.2, C2315.2, C2316.1, U2301.35 (REFGND); also elsewhere on the board
GNDPWR: C2302.2, C2303.2, C2304.2, C2306.2, C2307.2, C2308.2, C2309.2, C2310.2, C2311.2, C2312.2, C2313.2, C2314.2, U2301.10 (GND), U2301.15 (TOGGLE0), U2301.16 (TOGGLE1), U2301.17 (TOGGLE2), U2301.36 (GND); also elsewhere on the board
MISO-0: U2301.11 (SDO); also elsewhere on the board
unnamed: C2315.1, U2301.34 (REFCMP)
SCLK-0: U2301.12 (SCLK); also elsewhere on the board

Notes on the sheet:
VDD
VIO-voltage supply decoupling
VAA
VAA+VDD supply decoupling
VCC+VSS-supply decoupling
